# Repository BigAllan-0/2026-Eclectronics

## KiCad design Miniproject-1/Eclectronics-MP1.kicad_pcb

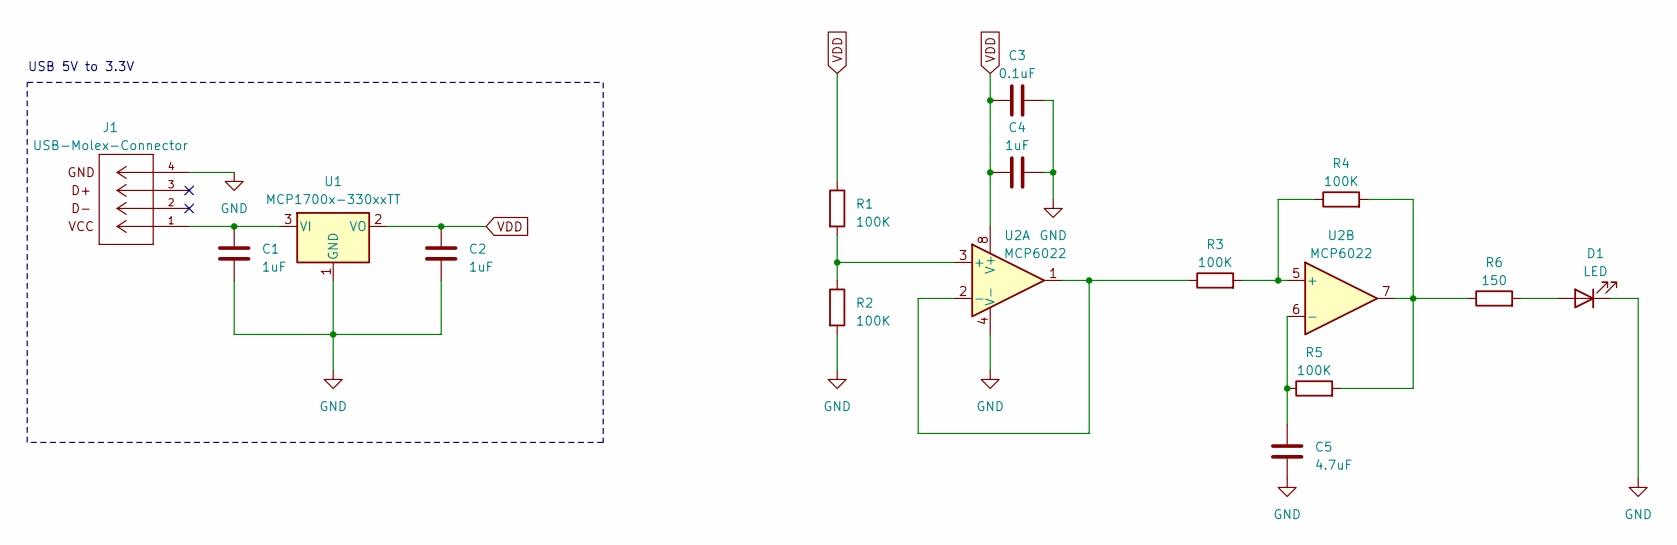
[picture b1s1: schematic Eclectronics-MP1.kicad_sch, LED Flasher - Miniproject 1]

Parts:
C1, C2, C4: 1uF; C_0603_1608Metric
C3: 0.1uF; C_0603_1608Metric
C5: 4.7uF; C_0603_1608Metric
D1: LED; D_0805_2012Metric
J1: USB-Molex-Connector; USB_CONN_480370001_MOL; MANUFACTURER_PART_NUMBER 480370001
R1, R2, R3, R4, R5: 100K; R_0603_1608Metric
R6: 150; R_0603_1608Metric
U1: MCP1700x-330xxTT; SOT-23
U2: MCP6022; TSSOP8_MC_MCH

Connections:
GND: C1.2, C2.2, C3.2, C4.2, C5.1, D1.1 (K), J1.4, R2.2, U1.1 (GND), U2.4 (V-)
unnamed: D1.2 (A), R6.2
unnamed: R4.2, R5.2, R6.1, U2.7
unnamed: C1.1, J1.1, U1.3 (VI)
unnamed: R1.2, R2.1, U2.3 (+)
unnamed: R3.1, U2.1, U2.2 (-)
unnamed: R3.2, R4.1, U2.5 (+)
unnamed: C5.2, R5.1, U2.6 (-)
VDD: C2.1, C3.1, C4.1, R1.1, U1.2 (VO), U2.8 (V+)

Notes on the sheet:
USB 5V to 3.3V

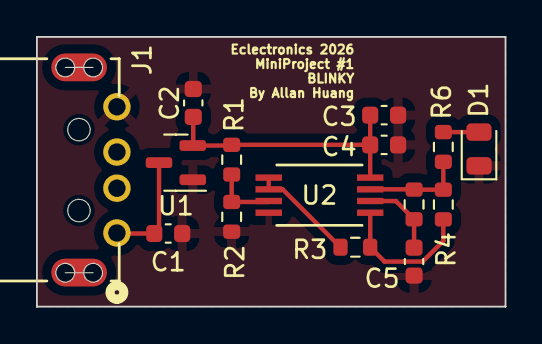
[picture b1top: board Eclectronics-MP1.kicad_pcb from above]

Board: 2 copper layers, 26.0 x 15.0 mm, 15 parts (0 on the bottom side), 9 nets.

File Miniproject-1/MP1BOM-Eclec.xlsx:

Source: | C:\Users\ahuang2\OneDrive - Olin College of Engineering\Documents\KiCad\Project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
Date: | 46062.404166666667
Tool: | Eeschema (7.0.0)
Generator: | C:\Program Files\KiCad\7.0\bin\scripting\plugins/bom_csv_grouped_by_value.py
Component Count: | 15
Collated Components:
Item | Qty | Reference(s) | Value | LibPart | Footprint | Datasheet | DNP | MANUFACTURER_PART_NUMBER | MFR_NAME
1 | 3 | C1, C2, C4 | 1uF | Device:C | Capacitor_SMD:C_0603_1608Metric | ~
2 | 1 | C3 | 0.1uF | Device:C | Capacitor_SMD:C_0603_1608Metric | ~
3 | 1 | C5 | 4.7uF | Device:C | Capacitor_SMD:C_0603_1608Metric | ~
4 | 1 | D1 | LED | Device:LED | Diode_SMD:D_0805_2012Metric | ~
5 | 1 | J1 | USB-Molex-Connector | 480370001:USB-Molex-Connector | Eclectronics - Olin Semester 8:USB_CONN_480370001_MOL |  |  |  | 480370001 | Molex Connector Corporation
6 | 5 | R1, R2, R3, R4, R5 | 100K | Device:R | Resistor_SMD:R_0603_1608Metric | ~
7 | 1 | R6 | 150 | Device:R | Resistor_SMD:R_0603_1608Metric | ~
8 | 1 | U1 | MCP1702T-3302E | Regulator_Linear:MCP1700x-330xxTT | Package_TO_SOT_SMD:SOT-23 | http://ww1.microchip.com/downloads/en/DeviceDoc/20001826D.pdf
9 | 1 | U2 | MCP6022 | Amplifier_Operational:MCP6022 | Eclectronics - Olin Semester 8:TSSOP8_MC_MCH | http://ww1.microchip.com/downloads/en/devicedoc/20001685e.pdf

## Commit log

2026-02-09 Create Test
2026-02-09 Adding Miniproject 1 Files
    Adding KiCad files, LTSpice files, and images of plots (Data collected from Monte Carlo sim was too large, huge text file causing error)
2026-02-09 Adding New BOM
2026-02-09 Create Miniproject-1-Fixed
